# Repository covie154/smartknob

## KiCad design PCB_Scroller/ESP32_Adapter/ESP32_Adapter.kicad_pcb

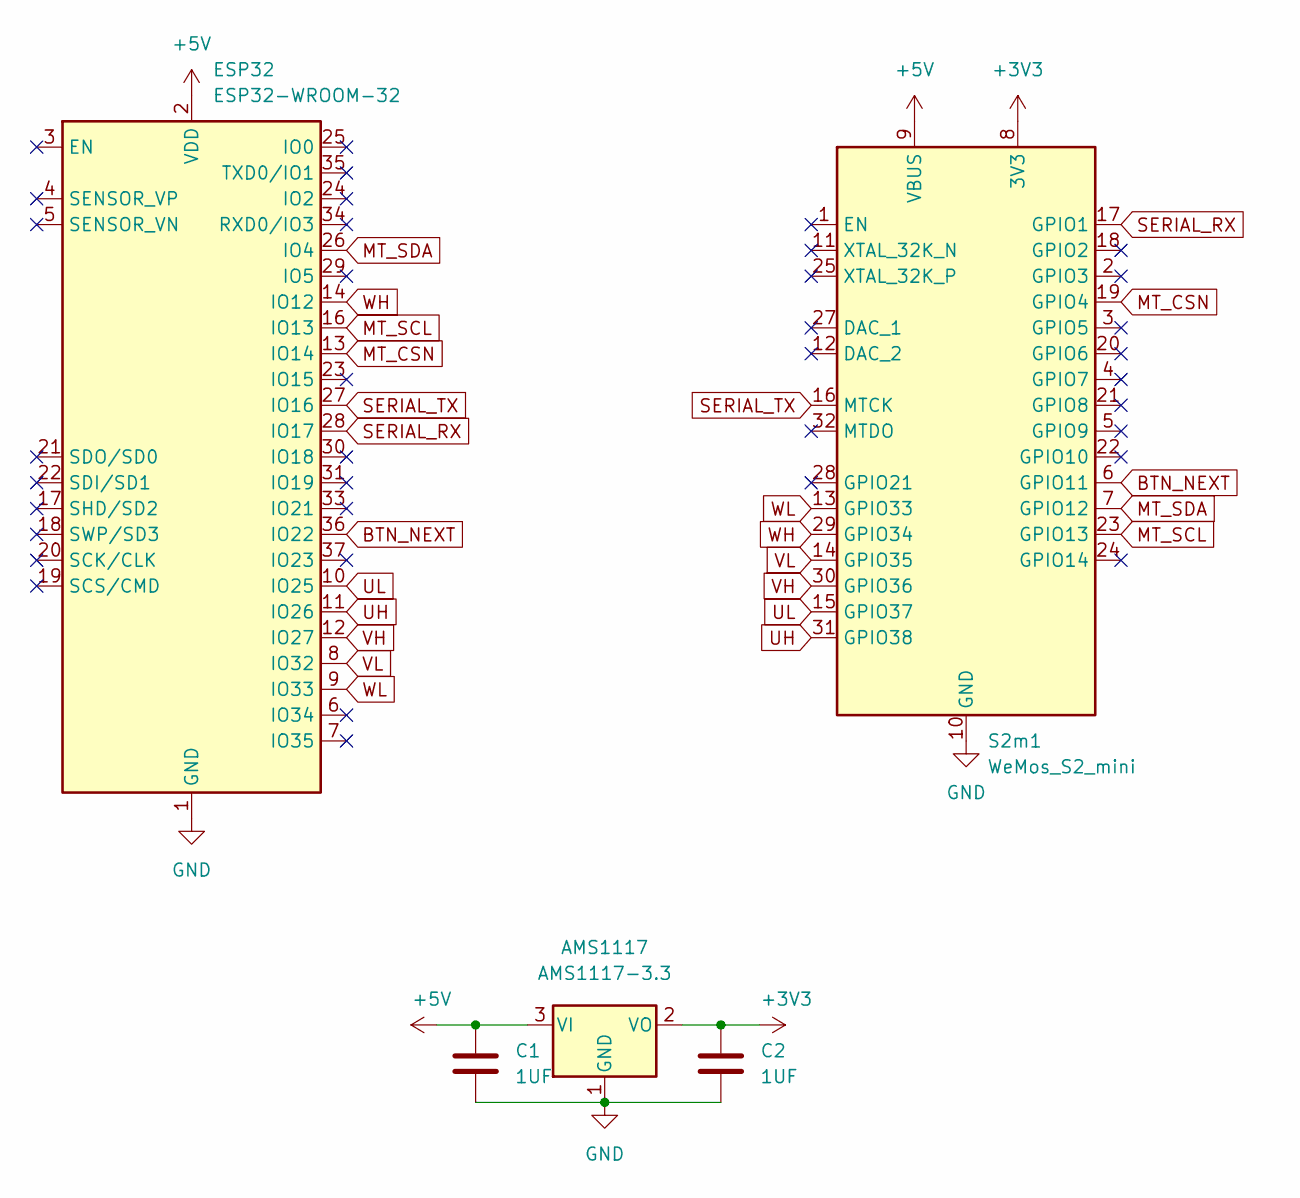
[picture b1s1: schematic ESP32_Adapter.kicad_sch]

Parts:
AMS1117: AMS1117-3.3; SOT-223-3_TabPin2
C1, C2: 1UF; C_0603_1608Metric_Pad1.08x0.95mm_HandSolder
ESP32: ESP32-WROOM-32
S2m1: WeMos_S2_mini; WEMOS_S2_mini

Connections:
+3V3: AMS1117.2 (VO), C2.1, S2m1.8 (3V3)
+5V: AMS1117.3 (VI), C1.1, ESP32.2 (VDD), S2m1.9 (VBUS)
BTN_NEXT: ESP32.36 (IO22), S2m1.6 (GPIO11)
GND: AMS1117.1 (GND), C1.2, C2.2, ESP32.1 (GND), ESP32.15 (GND), ESP32.38 (GND), ESP32.39 (GND), S2m1.10 (GND), S2m1.26 (GND)
MT_CSN: ESP32.13 (IO14), S2m1.19 (GPIO4)
MT_SCL: ESP32.16 (IO13), S2m1.23 (GPIO13)
MT_SDA: ESP32.26 (IO4), S2m1.7 (GPIO12)
SERIAL_RX: ESP32.28 (IO17), S2m1.17 (GPIO1)
SERIAL_TX: ESP32.27 (IO16), S2m1.16 (MTCK)
UH: ESP32.11 (IO26), S2m1.31 (GPIO38)
UL: ESP32.10 (IO25), S2m1.15 (GPIO37)
VH: ESP32.12 (IO27), S2m1.30 (GPIO36)
VL: ESP32.8 (IO32), S2m1.14 (GPIO35)
WH: ESP32.14 (IO12), S2m1.29 (GPIO34)
WL: ESP32.9 (IO33), S2m1.13 (GPIO33)

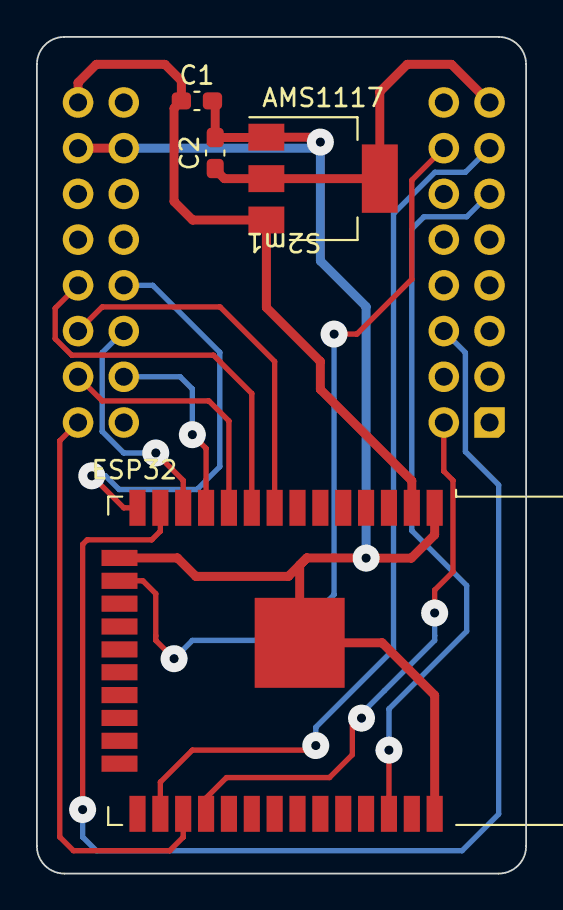
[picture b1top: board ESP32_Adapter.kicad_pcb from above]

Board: 2 copper layers, 27.2 x 46.5 mm, 5 parts (0 on the bottom side), 15 nets.

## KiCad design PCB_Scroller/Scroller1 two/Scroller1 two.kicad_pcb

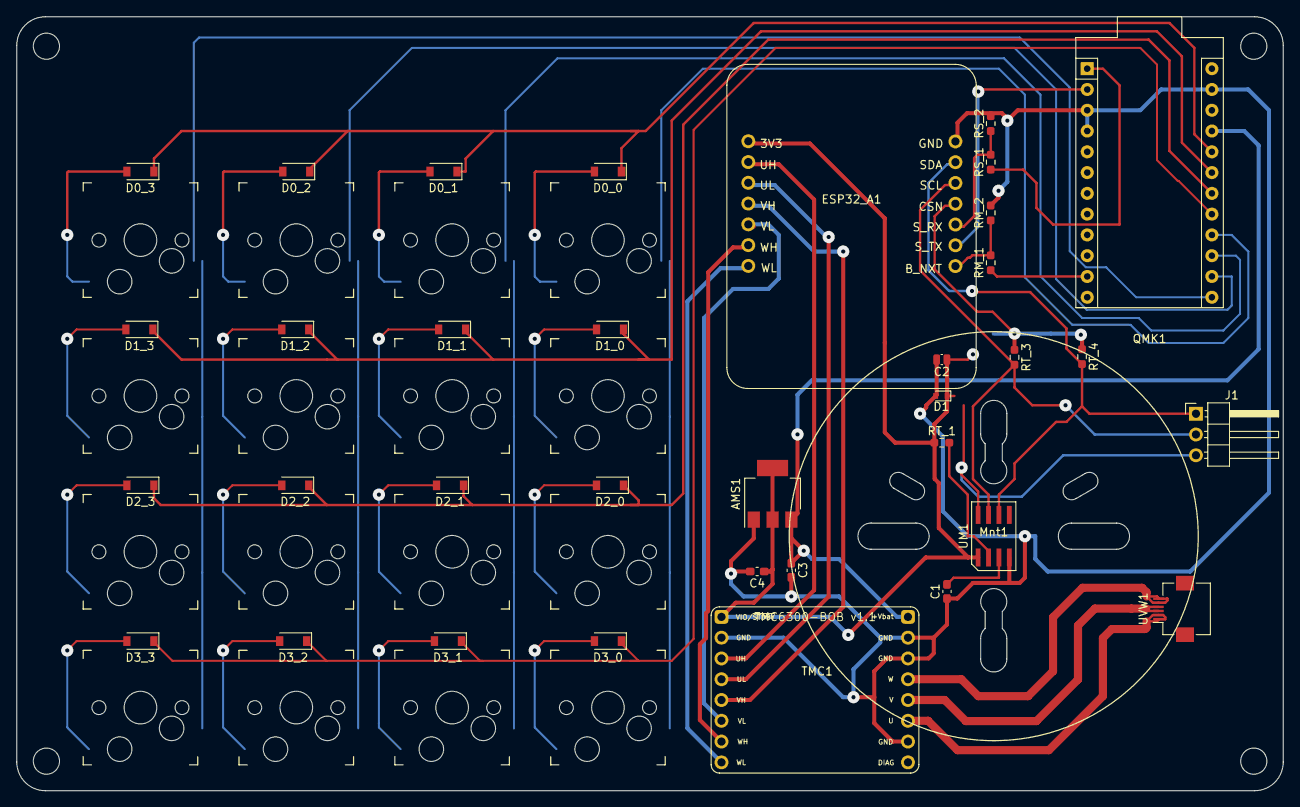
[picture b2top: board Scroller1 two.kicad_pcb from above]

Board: 2 copper layers, 154.8 x 94.6 mm, 56 parts (0 on the bottom side), 44 nets.

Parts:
AMS1: AMS1117-3.3; SOT-223-3_TabPin2
C1: 100nF; C_0603_1608Metric_Pad1.08x0.95mm_HandSolder
C2: 1uF; C_0504_1310Metric_Pad0.83x1.28mm_HandSolder
C3, C4: 1UF; C_0603_1608Metric_Pad1.08x0.95mm_HandSolder
D0_0, D0_1, D0_2, D0_3, D1_0, D1_1, D1_2, D1_3, D2_0, D2_1, D2_2, D2_3, D3_0, D3_1, D3_2, D3_3: 1N4148; D_SOD-123
D1: ZMDxx; D_SOD-523
ESP32_A1: ESP32_Adapter; ESP32 Motor Adapter
J1: 3 Pin Male; PinHeader_1x03_P2.54mm_Horizontal
MHole_1, MHole_3, MHole_4, MHole_6: M3; MountingHole_3.2mm_M3
Mnt1: -; BLDC Mount
QMK1: Sparkfun_Pro_Micro
RM_1, RM_2: 10k; R_0603_1608Metric_Pad0.98x0.95mm_HandSolder
RS_1, RS_2: 10k; R_0603_1608Metric_Pad0.98x0.95mm_HandSolder
RT_1: 100k; R_0603_1608Metric_Pad0.98x0.95mm_HandSolder
RT_3, RT_4: 4k7; R_0603_1608Metric_Pad0.98x0.95mm_HandSolder
SW_0_0, SW_0_1, SW_0_2, SW_0_3, SW_1_0, SW_1_1, SW_1_2, SW_1_3, SW_2_0, SW_2_1, SW_2_2, SW_2_3, SW_3_0, SW_3_1, SW_3_2, SW_3_3: SW_SPST; Kailh_socket_MX
TMC1: TMC6300_BOB
UM1: MT6701; SOIC-8
UVW1: FPC-6P; Hirose_FH12-6S-0.5SH_1x06-1MP_P0.50mm_Horizontal

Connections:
+5V: AMS1.3 (VI), C3.1, QMK1.21 (VCC), TMC1.9 (+VBAT)
/Col 1: QMK1.16 (D15), SW_0_0.2 (B), SW_1_0.2 (B), SW_2_0.2 (B), SW_3_0.2 (B)
/Col 2: QMK1.15 (D14), SW_0_1.2 (B), SW_1_1.2 (B), SW_2_1.2 (B), SW_3_1.2 (B)
/Col 3: QMK1.14 (D16), SW_0_2.2 (B), SW_1_2.2 (B), SW_2_2.2 (B), SW_3_2.2 (B)
/Col 4: QMK1.13 (~D10/A10), SW_0_3.2 (B), SW_1_3.2 (B), SW_2_3.2 (B), SW_3_3.2 (B)
/Row 1: D0_0.1 (K), D0_1.1 (K), D0_2.1 (K), D0_3.1 (K), QMK1.20 (D21/A3)
/Row 2: D1_0.1 (K), D1_1.1 (K), D1_2.1 (K), D1_3.1 (K), QMK1.19 (D20/A2)
/Row 3: D2_0.1 (K), D2_1.1 (K), D2_2.1 (K), D2_3.1 (K), QMK1.18 (D19/A1)
/Row 4: D3_0.1 (K), D3_1.1 (K), D3_2.1 (K), D3_3.1 (K), QMK1.17 (D18/A0)
/U_Out: TMC1.14 (W), UVW1.1, UVW1.2
/V_Out: TMC1.13 (V), UVW1.3, UVW1.4
/W_Out: TMC1.12 (W), UVW1.5, UVW1.6
BTN_NXT: RM_1.2, RM_2.1
CSn: AMS1.2 (VO), C2.1, C4.1, D1.1 (K), ESP32_A1.1 (3V3), J1.3, RT_1.1, RT_3.1, RT_4.1, TMC1.1 (+VCC_IO), UM1.1 (VDD), UM1.8 (Z/CSn)
GND: AMS1.1 (GND), C1.1, C2.2, C3.2, C4.2, D1.2 (A), QMK1.3 (GND), QMK1.4 (GND), QMK1.23 (GND), RM_2.2, RS_2.2, TMC1.2 (GND), TMC1.10 (GND), TMC1.11 (GND), TMC1.15 (GND), UM1.4 (GND)
unnamed: C1.2, UM1.3 (OUT)
unnamed: D0_0.2 (A), SW_0_0.1 (A)
unnamed: D0_1.2 (A), SW_0_1.1 (A)
unnamed: D0_2.2 (A), SW_0_2.1 (A)
unnamed: D0_3.2 (A), SW_0_3.1 (A)
unnamed: D1_0.2 (A), SW_1_0.1 (A)
unnamed: D1_1.2 (A), SW_1_1.1 (A)
unnamed: D1_2.2 (A), SW_1_2.1 (A)
unnamed: D1_3.2 (A), SW_1_3.1 (A)
unnamed: D2_0.2 (A), SW_2_0.1 (A)
unnamed: D2_1.2 (A), SW_2_1.1 (A)
unnamed: D2_2.2 (A), SW_2_2.1 (A)
unnamed: D2_3.2 (A), SW_2_3.1 (A)
unnamed: D3_0.2 (A), SW_3_0.1 (A)
unnamed: D3_1.2 (A), SW_3_1.1 (A)
unnamed: D3_2.2 (A), SW_3_2.1 (A)
unnamed: D3_3.2 (A), SW_3_3.1 (A)
unnamed: RS_1.2, RS_2.1
unnamed: QMK1.1 (D1/TX), RS_1.1
unnamed: QMK1.11 (D8/A8), RM_1.1
unnamed: RT_1.2, UM1.2 (MODE)
SCL: J1.2, RT_3.2, UM1.7 (B/SCL)
SDA: J1.1, RT_4.2, UM1.6 (A/SDA)
UH_in: ESP32_A1.2 (UH), TMC1.3 (UH_in)
UL_in: ESP32_A1.3 (UL), TMC1.4 (UL_in)
VH_in: ESP32_A1.4 (VH), TMC1.5 (VH_in)
VL_in: ESP32_A1.5 (VL), TMC1.6 (VL_in)
WH_in: ESP32_A1.6 (WH), TMC1.7 (WH_in)
WL_in: ESP32_A1.7 (WL), TMC1.8 (WL_in)

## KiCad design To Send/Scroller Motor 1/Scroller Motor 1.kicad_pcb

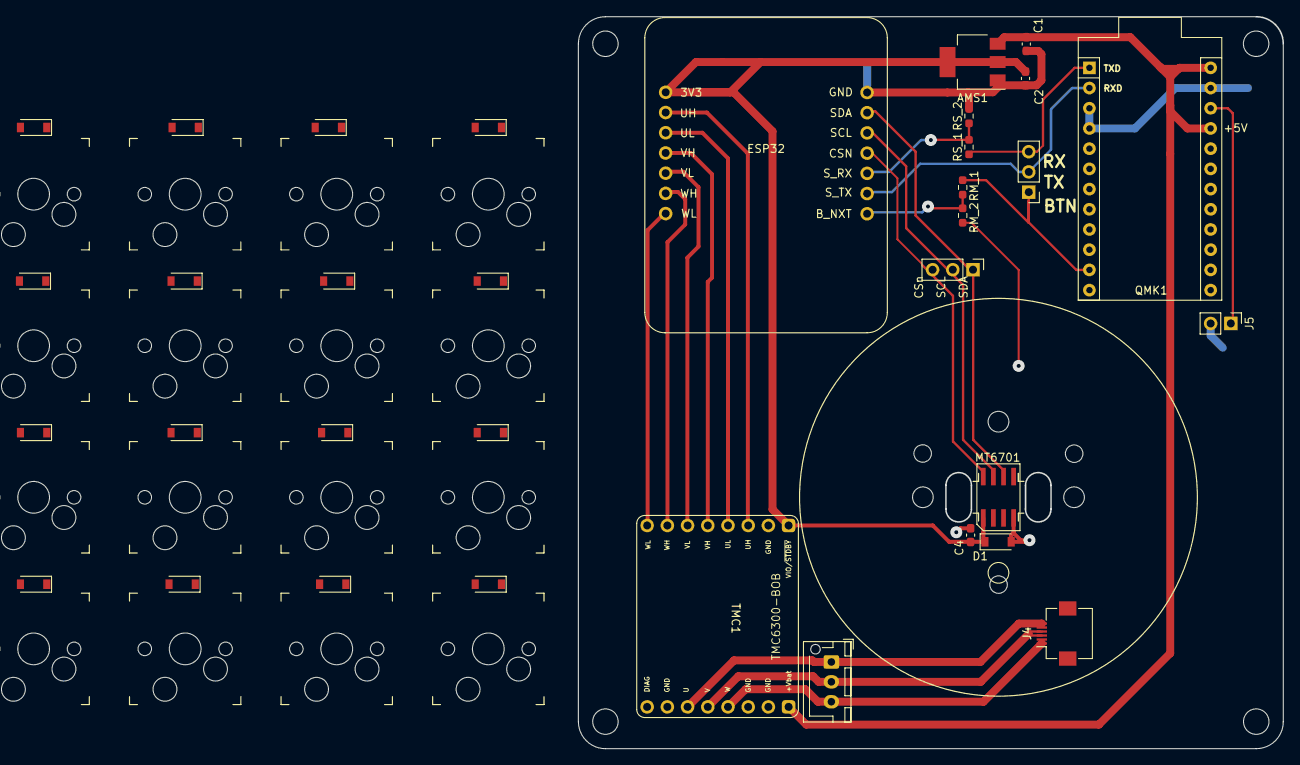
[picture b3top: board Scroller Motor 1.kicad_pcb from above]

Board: 2 copper layers, 88.6 x 92.0 mm, 25 parts (0 on the bottom side), 21 nets.

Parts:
AMS1: AMS1117-3.3; SOT-223-3_TabPin2
C1, C2: 1UF; C_0603_1608Metric_Pad1.08x0.95mm_HandSolder
C4: 1uF; C_0603_1608Metric_Pad1.08x0.95mm_HandSolder
D1: ZMDxx; D_SOD-123
ESP32: ESP32_Adapter; ESP32 Motor Adapter
J1: Conn_01x03_Male; JST_XH_B3B-XH-AM_1x03_P2.50mm_Vertical
J2: 3 Pin Male; PinHeader_1x03_P2.54mm_Vertical
J3: Conn_01x03_Male; PinHeader_1x03_P2.54mm_Vertical
J4: Conn_01x03_Male; Hirose_FH12-6S-0.5SH_1x06-1MP_P0.50mm_Horizontal
J5: Conn_01x02_Female; PinHeader_1x02_P2.54mm_Vertical
MHole_1, MHole_2, MHole_3, MHole_4: M3; MountingHole_3.2mm_M3
MT6701: MT6701; SOIC-8
Mnt0: Motor Mount; BLDC Mount 3
Mnt1: Alignment Jig; Jig Mnt
Mnt2: Motor Mount; BLDC 3514
QMK1: Sparkfun_Pro_Micro
RM_1, RM_2: 10k; R_0603_1608Metric_Pad0.98x0.95mm_HandSolder
RS_1, RS_2: 10k; R_0603_1608Metric_Pad0.98x0.95mm_HandSolder
TMC1: TMC6300_BOB

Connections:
+3V3: AMS1.2 (VO), C2.1, C4.1, D1.1 (K), ESP32.1 (3V3), MT6701.1 (VDD), TMC1.1 (+VCC_IO)
+5V: AMS1.3 (VI), C1.1, QMK1.21 (VCC), QMK1.24 (RAW), TMC1.9 (+VBAT)
/U_Out: J1.1, J4.5, J4.6, TMC1.14 (W)
/V_Out: J1.2, J4.3, J4.4, TMC1.13 (V)
/W_Out: J1.3, J4.1, J4.2, TMC1.12 (W)
A_RST: J5.1, QMK1.22 (RST)
BTN_NEXT_O: J3.1, QMK1.11 (D8/A8), RM_1.1
BTN_NXT: ESP32.14 (B_NXT), RM_1.2, RM_2.1
CSn: ESP32.11 (CSN), J2.3, MT6701.8 (Z/CSn)
GND: AMS1.1 (GND), C1.2, C2.2, C4.2, D1.2 (A), ESP32.8 (GND), J5.2, MT6701.4 (GND), QMK1.3 (GND), QMK1.4 (GND), QMK1.23 (GND), RM_2.2, RS_2.2, TMC1.2 (GND), TMC1.10 (GND), TMC1.11 (GND), TMC1.15 (GND)
unnamed: ESP32.12 (S_RX), RS_1.2, RS_2.1
SCL: ESP32.10 (SCL), J2.2, MT6701.7 (B/SCL)
SDA: ESP32.9 (SDA), J2.1, MT6701.6 (A/SDA)
SERIAL_RX: J3.3, QMK1.1 (D1/TX), RS_1.1
SERIAL_TX: ESP32.13 (S_TX), J3.2, QMK1.2 (D0/RX)
UH_in: ESP32.2 (UH), TMC1.3 (UH_in)
UL_in: ESP32.3 (UL), TMC1.4 (UL_in)
VH_in: ESP32.4 (VH), TMC1.5 (VH_in)
VL_in: ESP32.5 (VL), TMC1.6 (VL_in)
WH_in: ESP32.6 (WH), TMC1.7 (WH_in)
WL_in: ESP32.7 (WL), TMC1.8 (WL_in)

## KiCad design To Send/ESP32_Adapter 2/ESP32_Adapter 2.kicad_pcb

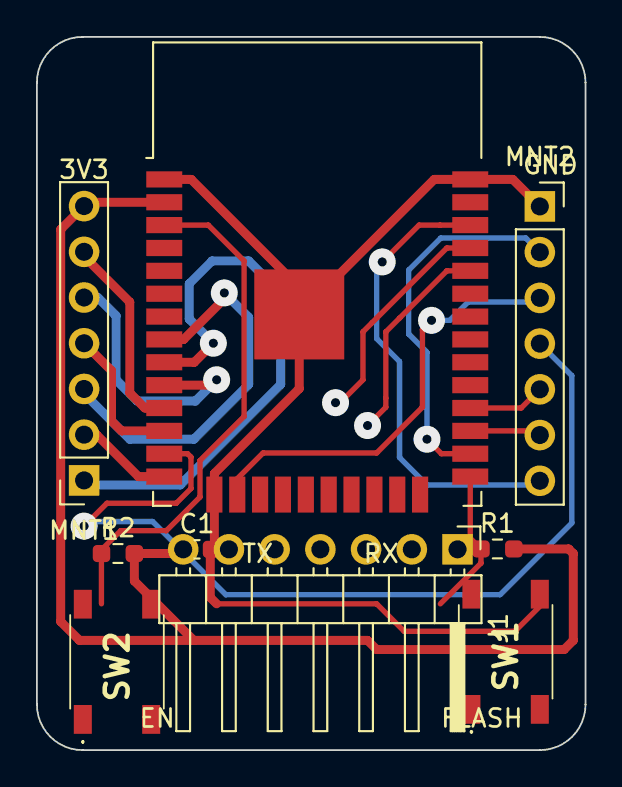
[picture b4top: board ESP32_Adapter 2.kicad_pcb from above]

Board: 2 copper layers, 30.5 x 39.6 mm, 9 parts (0 on the bottom side), 18 nets.

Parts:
C1: 0.1UF; C_0603_1608Metric_Pad1.08x0.95mm_HandSolder
ESP32: ESP32-WROOM-32
J1: Conn_01x06_Male; PinHeader_1x07_P2.54mm_Horizontal
MNT1, MNT2: Conn_01x07_Female; PinSocket_1x07_P2.54mm_Vertical
R1, R2: 10K; R_0603_1608Metric_Pad0.98x0.95mm_HandSolder
SW1, SW2: SW_SPST; PTS525SM08SMTR2LFS

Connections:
+3V3: C1.1, ESP32.2 (VDD), J1.1, MNT1.7, R1.2, R2.2
BTN_NEXT: ESP32.36 (IO22), MNT2.7
EN: ESP32.3 (EN), J1.4, R2.1, SW2.1
FLASH: ESP32.25 (IO0), J1.5, R1.1, SW1.1
GND: C1.2, ESP32.1 (GND), ESP32.15 (GND), ESP32.38 (GND), ESP32.39 (GND), J1.6, MNT2.1, SW1.2, SW2.2
MT_CSN: ESP32.13 (IO14), MNT2.4
MT_SCL: ESP32.16 (IO13), MNT2.3
MT_SDA: ESP32.26 (IO4), MNT2.2
RXD: ESP32.34 (RXD0/IO3), J1.3
SERIAL_RX: ESP32.28 (IO17), MNT2.5
SERIAL_TX: ESP32.27 (IO16), MNT2.6
TXD: ESP32.35 (TXD0/IO1), J1.2
UH: ESP32.11 (IO26), MNT1.6
UL: ESP32.10 (IO25), MNT1.5
VH: ESP32.12 (IO27), MNT1.4
VL: ESP32.8 (IO32), MNT1.3
WH: ESP32.14 (IO12), MNT1.2
WL: ESP32.9 (IO33), MNT1.1

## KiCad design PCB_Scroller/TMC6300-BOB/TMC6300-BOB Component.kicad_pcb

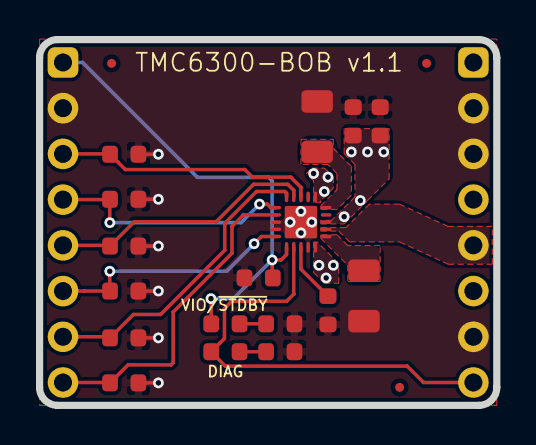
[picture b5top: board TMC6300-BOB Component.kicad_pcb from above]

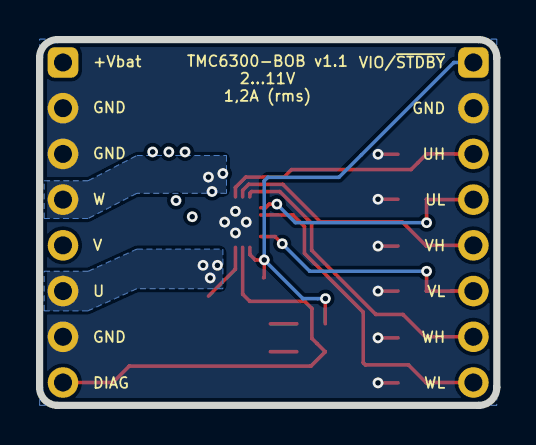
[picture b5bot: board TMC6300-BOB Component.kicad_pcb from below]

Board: 4 copper layers, 25.4 x 20.3 mm, 22 parts (2 on the bottom side), 18 nets.

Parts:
C101: 10μF/25V/0603; C_0603_1608Metric
C102, C104: 100nF/25V/0603; C_0603_1608Metric
C105: 100nF/10V/0603; C_0603_1608Metric
D101: White; LED_0603_1608Metric
D102: Blue; LED_0603_1608Metric
IC101: TMC6300; QFN20
J101, J102: Conn_01x08_Male; PinHeader_1x08_P2.54mm_Vertical
R101, R102, R103, R104, R105, R106: 100kΩ/1%/0603; R_0603_1608Metric
R107: 220Ω/1%/0603; R_0603_1608Metric
R108: 1kΩ/1%/0603; R_0603_1608Metric
R109, R110: 150mΩ/0,5W; R_1206_3216Metric
fid101, fid102, fid103: fiducial; Fiducial_0.5mm_Dia_1mm_Outer

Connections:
/+Vbat: C101.1, C102.1, IC101.18, J102.1
/DIAG: D101.2, IC101.12, J102.8
/U: IC101.15, J102.6
/UH: IC101.3, J101.3, R101.2
/UL: IC101.6, J101.4, R102.1
/V: IC101.17, J102.5
/VH: IC101.4, J101.5, R103.1
/VIO\~STDBY: C104.1, D102.2, IC101.11, J101.1
/VL: IC101.10, J101.6, R104.1
/W: IC101.1, J102.4
/WH: IC101.5, J101.7, R105.1
/WL: IC101.7, J101.8, R106.1
GND: C101.2, C102.2, C104.2, C105.2, IC101.8, IC101.9, IC101.14, IC101.PAD, J101.2, J102.2, J102.3, J102.7, R101.1, R102.2, R103.2, R104.2, R105.2, R106.2, R107.2, R108.2, R109.2, R110.2
unnamed: C105.1, IC101.13
unnamed: D101.1, R107.1
unnamed: D102.1, R108.1
unnamed: IC101.16, R110.1
unnamed: IC101.20, R109.1

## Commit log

2022-11-05 Version 1
2022-11-08 Updates
    Not sure if the ESP32 works...
2023-05-04 Update 040523
    Changed lots of things
2023-08-07 Updates 080723
